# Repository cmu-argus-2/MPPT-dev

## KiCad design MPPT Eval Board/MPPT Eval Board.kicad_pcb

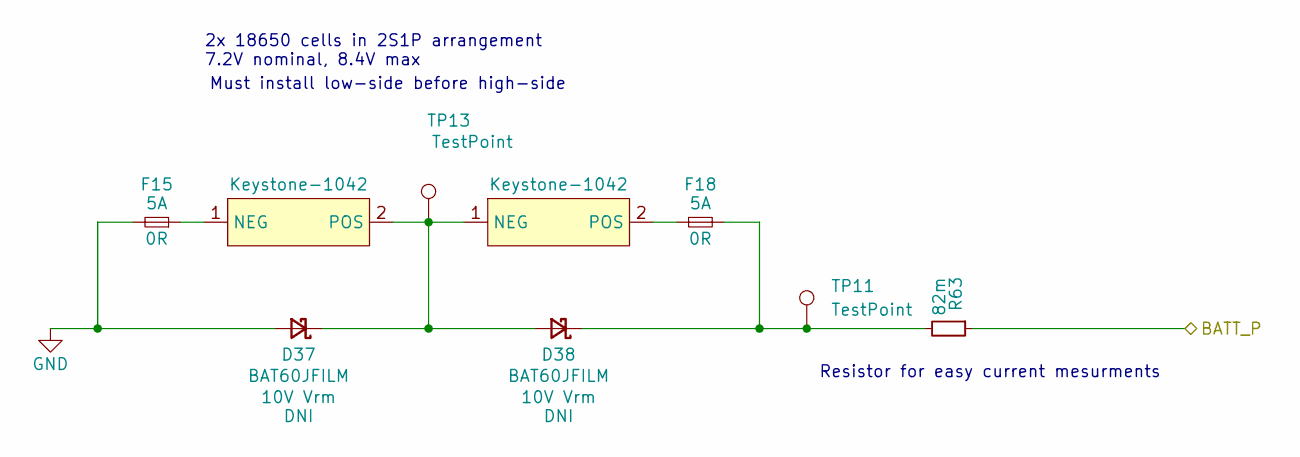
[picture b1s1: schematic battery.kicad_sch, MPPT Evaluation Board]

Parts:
D37, D38: BAT60JFILM; D_SOD-323_HandSoldering
F15, F18: 5A; Fuse_1206_3216Metric; MPN C844862
J3, J4: Keystone-1042; Keystone_1042
R63: 82m; R_0603_1608Metric
TP11, TP13: TestPoint; Pin_D1.0mm_L10.0mm

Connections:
/MPPC Implementation/VCHRG: R63.1; also elsewhere on the board
GND: D37.2 (A), F15.2; also elsewhere on the board
unnamed: D37.1 (K), D38.2 (A), J3.2 (POS), J4.1 (NEG), TP13.1 (1_1)
unnamed: D38.1 (K), F18.2, R63.2, TP11.1 (1_1)
unnamed: F15.1, J3.1 (NEG)
unnamed: F18.1, J4.2 (POS)

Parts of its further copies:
D39, D40: BAT60JFILM; D_SOD-323_HandSoldering
F16, F19: 5A; Fuse_1206_3216Metric; MPN C844862
J5, J6: Keystone-1042; Keystone_1042
R64: 82m; R_0603_1608Metric
TP12, TP14: TestPoint; Pin_D1.0mm_L10.0mm

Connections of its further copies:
/MPPT Implementation/VCHRG: R64.1; also elsewhere on the board
GND: D39.2 (A), F16.2; also elsewhere on the board
unnamed: D39.1 (K), D40.2 (A), J5.2 (POS), J6.1 (NEG), TP14.1 (1_1)
unnamed: D40.1 (K), F19.2, R64.2, TP12.1 (1_1)
unnamed: F16.1, J5.1 (NEG)
unnamed: F19.1, J6.2 (POS)

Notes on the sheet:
Must install low-side before high-side
Resistor for easy current mesurments
2x 18650 cells in 2S1P arrangement 7.2V nominal, 8.4V max

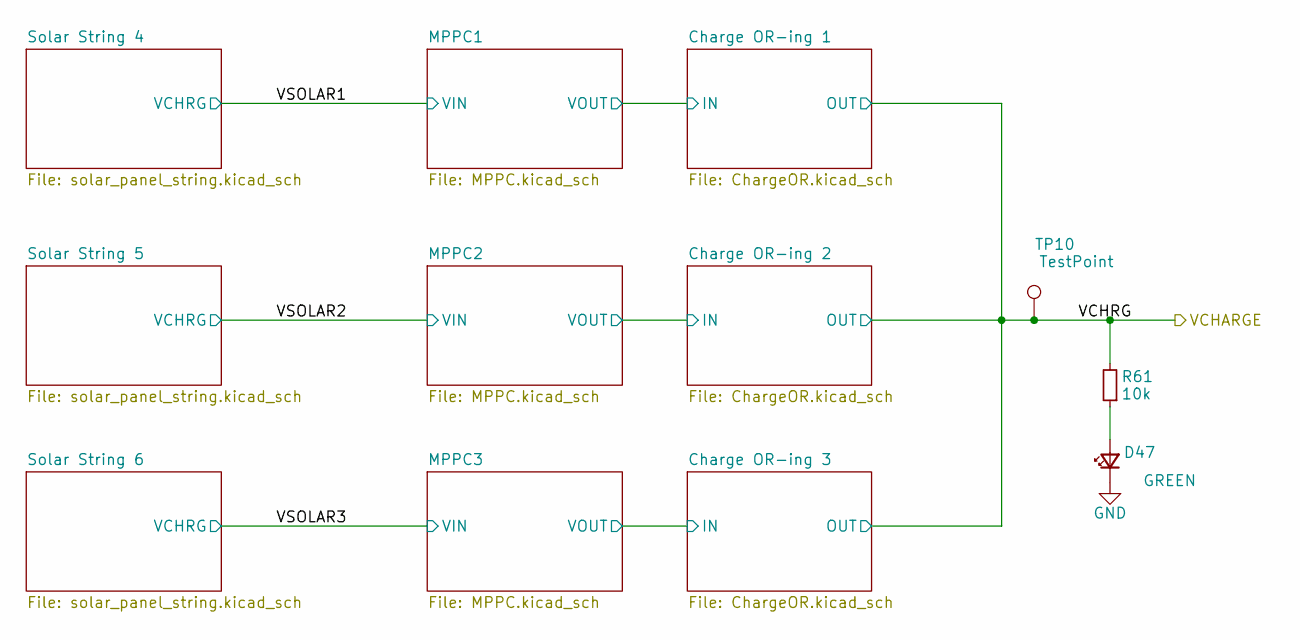
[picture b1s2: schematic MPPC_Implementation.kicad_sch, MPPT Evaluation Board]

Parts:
D47: GREEN; LED_0603_1608Metric; MPN C2909774
R61: 10k; R_0603_1608Metric; MPN C2479067
TP10: TestPoint; Pin_D1.0mm_L10.0mm

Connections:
/MPPC Implementation/VCHRG: R61.2, TP10.1 (1_1); also elsewhere on the board
GND: D47.1 (K); also elsewhere on the board
unnamed: D47.2 (A), R61.1

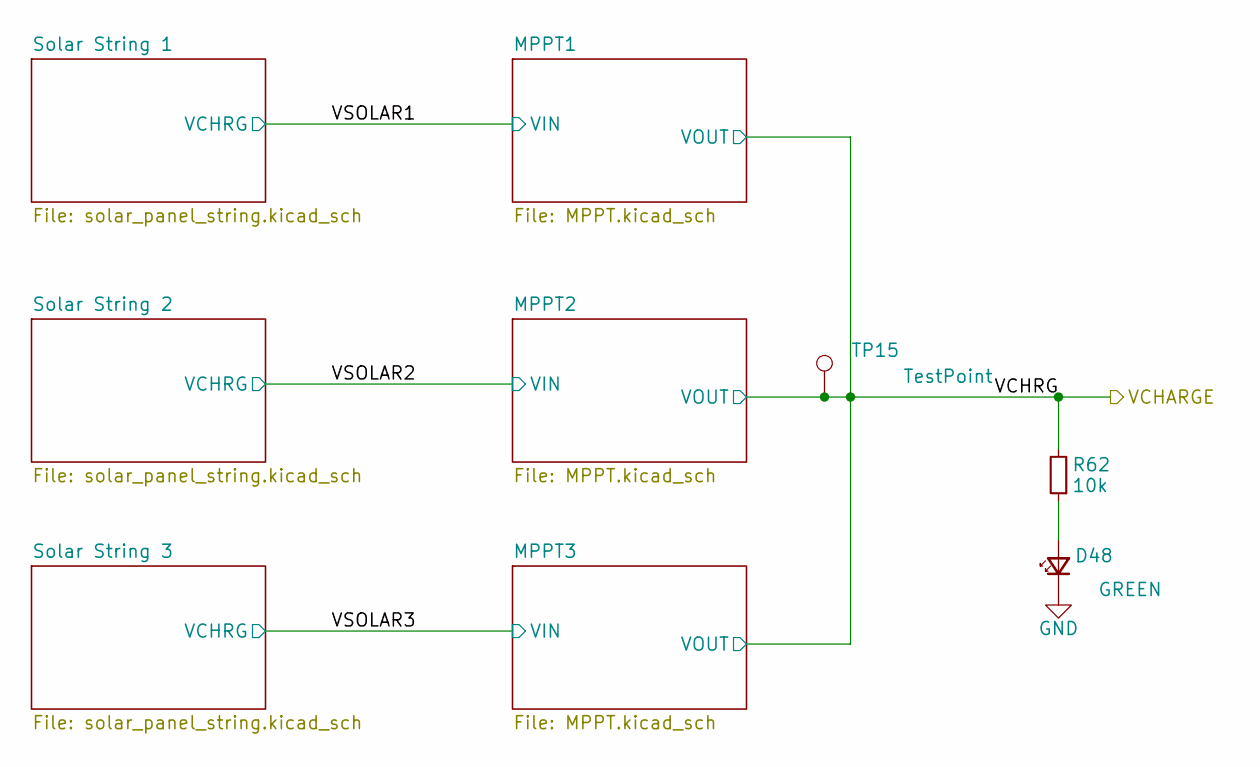
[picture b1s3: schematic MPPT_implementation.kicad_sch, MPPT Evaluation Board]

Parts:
D48: GREEN; LED_0603_1608Metric; MPN C2909774
R62: 10k; R_0603_1608Metric; MPN C2479067
TP15: TestPoint; Pin_D1.0mm_L10.0mm

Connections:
/MPPT Implementation/VCHRG: R62.2, TP15.1 (1_1); also elsewhere on the board
GND: D48.1 (K); also elsewhere on the board
unnamed: D48.2 (A), R62.1

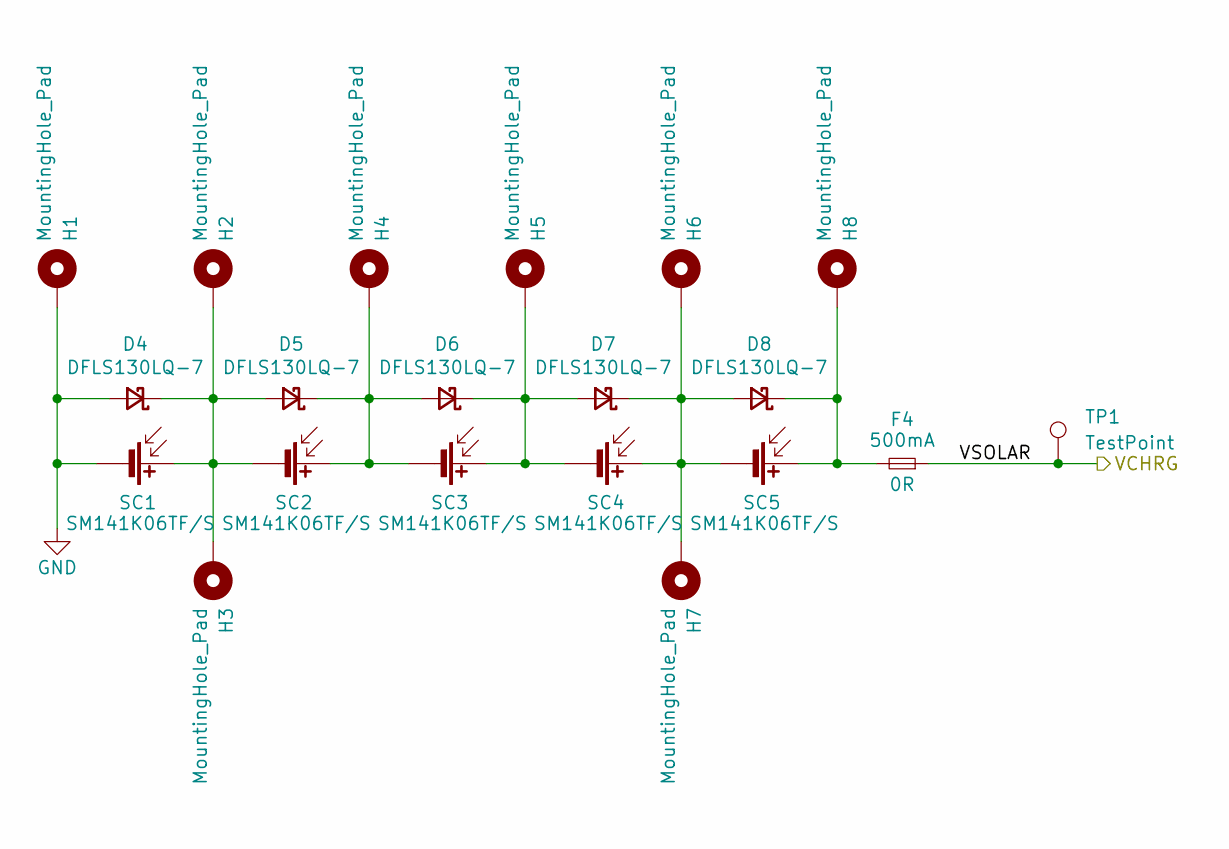
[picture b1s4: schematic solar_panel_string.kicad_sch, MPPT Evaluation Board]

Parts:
D4, D5, D6, D7, D8: DFLS130LQ-7; D_PowerDI-123
F4: 500mA; Fuse_0603_1608Metric
H1, H2, H3, H4, H5, H6, H7, H8: MountingHole_Pad; TestPoint_Pad_D1.0mm
SC1, SC2, SC3, SC4, SC5: SM141K06TF/S; SM141K06TF_S
TP1: TestPoint; Pin_D1.0mm_L10.0mm

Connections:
/MPPT Implementation/VSOLAR2: F4.1, TP1.1 (1_1); also elsewhere on the board
GND: D4.2 (A), H1.1 (1_1), SC1.2 (-); also elsewhere on the board
unnamed: D4.1 (K), D5.2 (A), H2.1 (1_1), H3.1 (1_1), SC1.1 (+), SC2.2 (-)
unnamed: D5.1 (K), D6.2 (A), H4.1 (1_1), SC2.1 (+), SC3.2 (-)
unnamed: D6.1 (K), D7.2 (A), H5.1 (1_1), SC3.1 (+), SC4.2 (-)
unnamed: D7.1 (K), D8.2 (A), H6.1 (1_1), H7.1 (1_1), SC4.1 (+), SC5.2 (-)
unnamed: D8.1 (K), F4.2, H8.1 (1_1), SC5.1 (+)

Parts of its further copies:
D10, D11, D12, D13, D14, D15, D16, D17, D18, D19, D22, D23, D24, D25, D26, D27, D28, D29, D30, D31, D32, D33, D34, D35, D36: DFLS130LQ-7; D_PowerDI-123
F6, F7, F10, F11, F12: 500mA; Fuse_0603_1608Metric
H9, H10, H11, H12, H13, H14, H15, H16, H17, H18, H19, H20, H21, H22, H23, H24, H25, H26, H27, H28, H29, H30, H31, H32, H33, H34, H35, H36, H37, H38, H39, H40, H41, H42, H43, H44, H45, H46, H47, H48: MountingHole_Pad; TestPoint_Pad_D1.0mm
SC6, SC7, SC8, SC9, SC10, SC11, SC12, SC13, SC14, SC15, SC16, SC17, SC18, SC19, SC20, SC21, SC22, SC23, SC24, SC25, SC26, SC27, SC28, SC29, SC30: SM141K06TF/S; SM141K06TF_S
TP2, TP3, TP4, TP5, TP6: TestPoint; Pin_D1.0mm_L10.0mm

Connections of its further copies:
/MPPC Implementation/VSOLAR1: F10.1, TP4.1 (1_1); also elsewhere on the board
/MPPC Implementation/VSOLAR2: F11.1, TP5.1 (1_1); also elsewhere on the board
/MPPC Implementation/VSOLAR3: F12.1, TP6.1 (1_1); also elsewhere on the board
/MPPT Implementation/VSOLAR1: F6.1, TP2.1 (1_1); also elsewhere on the board
/MPPT Implementation/VSOLAR3: F7.1, TP3.1 (1_1); also elsewhere on the board
GND: D10.2 (A), D15.2 (A), D22.2 (A), D27.2 (A), D32.2 (A), H9.1 (1_1), H17.1 (1_1), H25.1 (1_1), H33.1 (1_1), H41.1 (1_1), SC6.2 (-), SC11.2 (-), SC16.2 (-), SC21.2 (-), SC26.2 (-); also elsewhere on the board
unnamed: D10.1 (K), D11.2 (A), H10.1 (1_1), H11.1 (1_1), SC6.1 (+), SC7.2 (-)
unnamed: D11.1 (K), D12.2 (A), H12.1 (1_1), SC7.1 (+), SC8.2 (-)
unnamed: D12.1 (K), D13.2 (A), H13.1 (1_1), SC8.1 (+), SC9.2 (-)
unnamed: D13.1 (K), D14.2 (A), H14.1 (1_1), H15.1 (1_1), SC9.1 (+), SC10.2 (-)
unnamed: D14.1 (K), F6.2, H16.1 (1_1), SC10.1 (+)
unnamed: D15.1 (K), D16.2 (A), H18.1 (1_1), H19.1 (1_1), SC11.1 (+), SC12.2 (-)
unnamed: D16.1 (K), D17.2 (A), H20.1 (1_1), SC12.1 (+), SC13.2 (-)
unnamed: D17.1 (K), D18.2 (A), H21.1 (1_1), SC13.1 (+), SC14.2 (-)
unnamed: D18.1 (K), D19.2 (A), H22.1 (1_1), H23.1 (1_1), SC14.1 (+), SC15.2 (-)
unnamed: D19.1 (K), F7.2, H24.1 (1_1), SC15.1 (+)
unnamed: D22.1 (K), D23.2 (A), H26.1 (1_1), H27.1 (1_1), SC16.1 (+), SC17.2 (-)
unnamed: D23.1 (K), D24.2 (A), H28.1 (1_1), SC17.1 (+), SC18.2 (-)
unnamed: D24.1 (K), D25.2 (A), H29.1 (1_1), SC18.1 (+), SC19.2 (-)
unnamed: D25.1 (K), D26.2 (A), H30.1 (1_1), H31.1 (1_1), SC19.1 (+), SC20.2 (-)
unnamed: D26.1 (K), F10.2, H32.1 (1_1), SC20.1 (+)
unnamed: D27.1 (K), D28.2 (A), H34.1 (1_1), H35.1 (1_1), SC21.1 (+), SC22.2 (-)
unnamed: D28.1 (K), D29.2 (A), H36.1 (1_1), SC22.1 (+), SC23.2 (-)
unnamed: D29.1 (K), D30.2 (A), H37.1 (1_1), SC23.1 (+), SC24.2 (-)
unnamed: D30.1 (K), D31.2 (A), H38.1 (1_1), H39.1 (1_1), SC24.1 (+), SC25.2 (-)
unnamed: D31.1 (K), F11.2, H40.1 (1_1), SC25.1 (+)
unnamed: D32.1 (K), D33.2 (A), H42.1 (1_1), H43.1 (1_1), SC26.1 (+), SC27.2 (-)
unnamed: D33.1 (K), D34.2 (A), H44.1 (1_1), SC27.1 (+), SC28.2 (-)
unnamed: D34.1 (K), D35.2 (A), H45.1 (1_1), SC28.1 (+), SC29.2 (-)
unnamed: D35.1 (K), D36.2 (A), H46.1 (1_1), H47.1 (1_1), SC29.1 (+), SC30.2 (-)
unnamed: D36.1 (K), F12.2, H48.1 (1_1), SC30.1 (+)

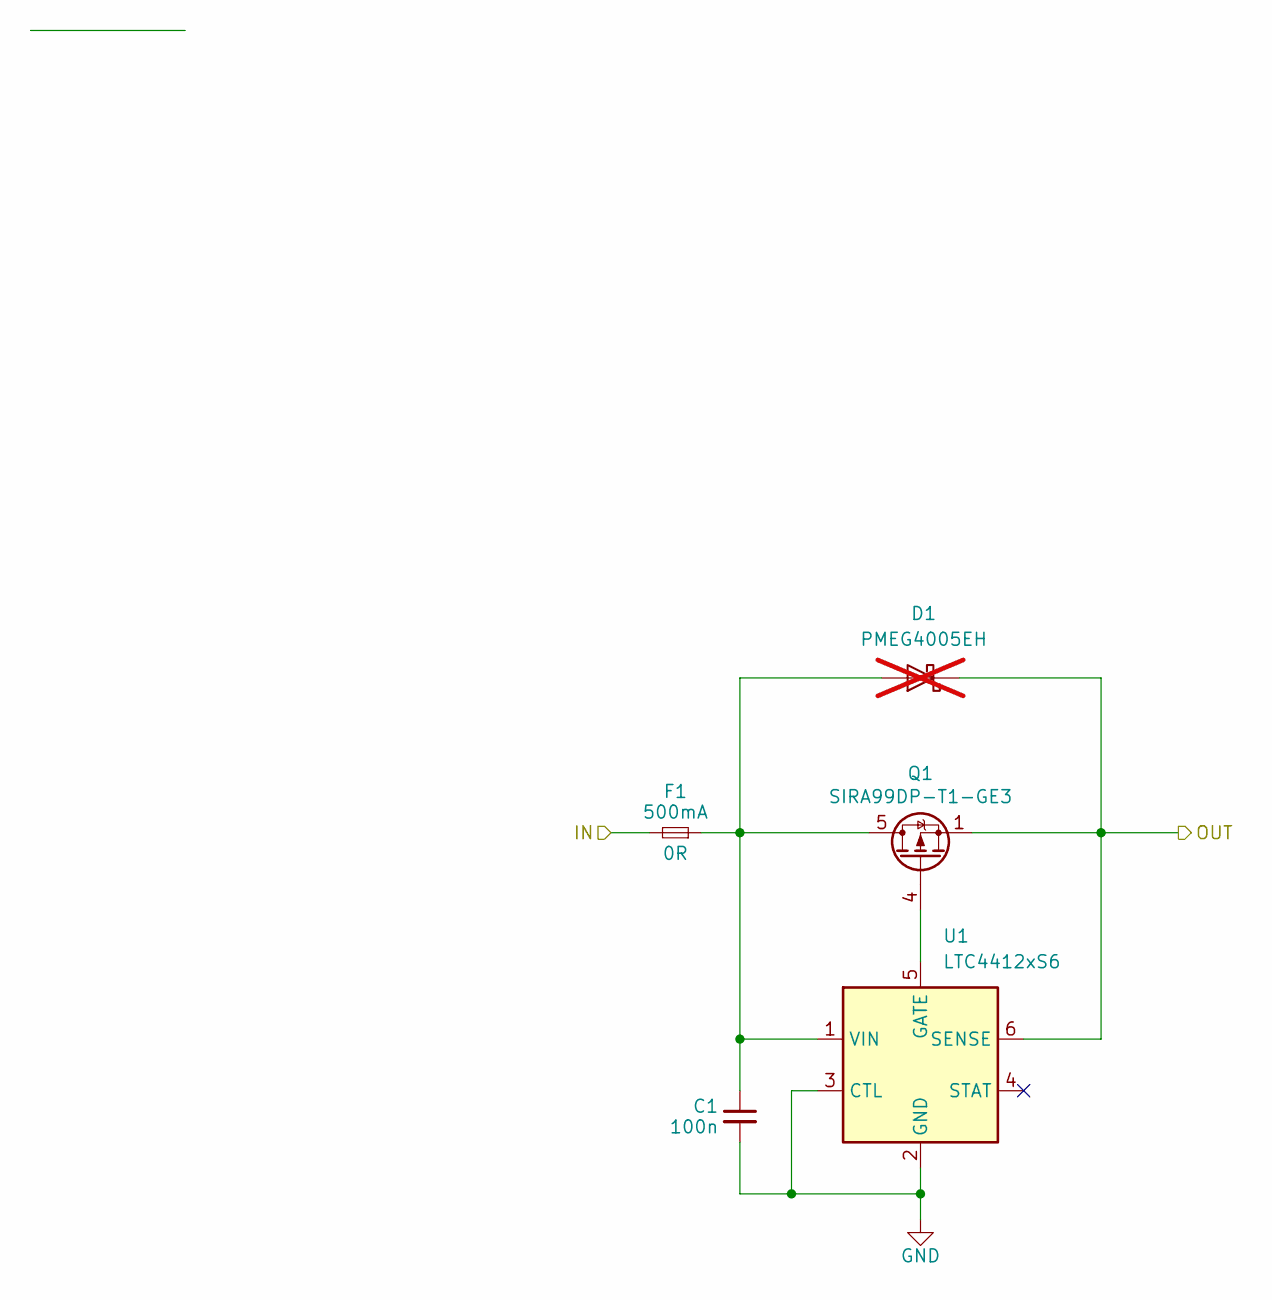
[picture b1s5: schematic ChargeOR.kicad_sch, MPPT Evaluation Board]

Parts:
C1: 100n; C_0603_1608Metric; MPN C307348
D1: PMEG4005EH; D_SOD-123F; not fitted
F1: 500mA; Fuse_0603_1608Metric
Q1: SIRA99DP-T1-GE3; PowerPAK_SO-8_Single; MPN C3289459
U1: LTC4412xS6; TSOT-23-6

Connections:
/MPPC Implementation/Charge OR-ing 1/IN: F1.2; also elsewhere on the board
/MPPC Implementation/VCHRG: D1.1 (K), Q1.1 (S), Q1.2 (S), Q1.3 (S), U1.6 (SENSE); also elsewhere on the board
GND: C1.2, U1.2 (GND), U1.3 (CTL); also elsewhere on the board
unnamed: C1.1, D1.2 (A), F1.1, Q1.5 (D), U1.1 (VIN)
unnamed: Q1.4 (G), U1.5 (GATE)

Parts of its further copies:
C17, C18: 100n; C_0603_1608Metric; MPN C307348
D20, D21: PMEG4005EH; D_SOD-123F; not fitted
F8, F9: 500mA; Fuse_0603_1608Metric
Q11, Q12: SIRA99DP-T1-GE3; PowerPAK_SO-8_Single; MPN C3289459
U8, U9: LTC4412xS6; TSOT-23-6

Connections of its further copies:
/MPPC Implementation/Charge OR-ing 2/IN: F8.2; also elsewhere on the board
/MPPC Implementation/Charge OR-ing 3/IN: F9.2; also elsewhere on the board
/MPPC Implementation/VCHRG: D20.1 (K), D21.1 (K), Q11.1 (S), Q11.2 (S), Q11.3 (S), Q12.1 (S), Q12.2 (S), Q12.3 (S), U8.6 (SENSE), U9.6 (SENSE); also elsewhere on the board
GND: C17.2, C18.2, U8.2 (GND), U8.3 (CTL), U9.2 (GND), U9.3 (CTL); also elsewhere on the board
unnamed: C17.1, D20.2 (A), F8.1, Q11.5 (D), U8.1 (VIN)
unnamed: C18.1, D21.2 (A), F9.1, Q12.5 (D), U9.1 (VIN)
unnamed: Q11.4 (G), U8.5 (GATE)
unnamed: Q12.4 (G), U9.5 (GATE)

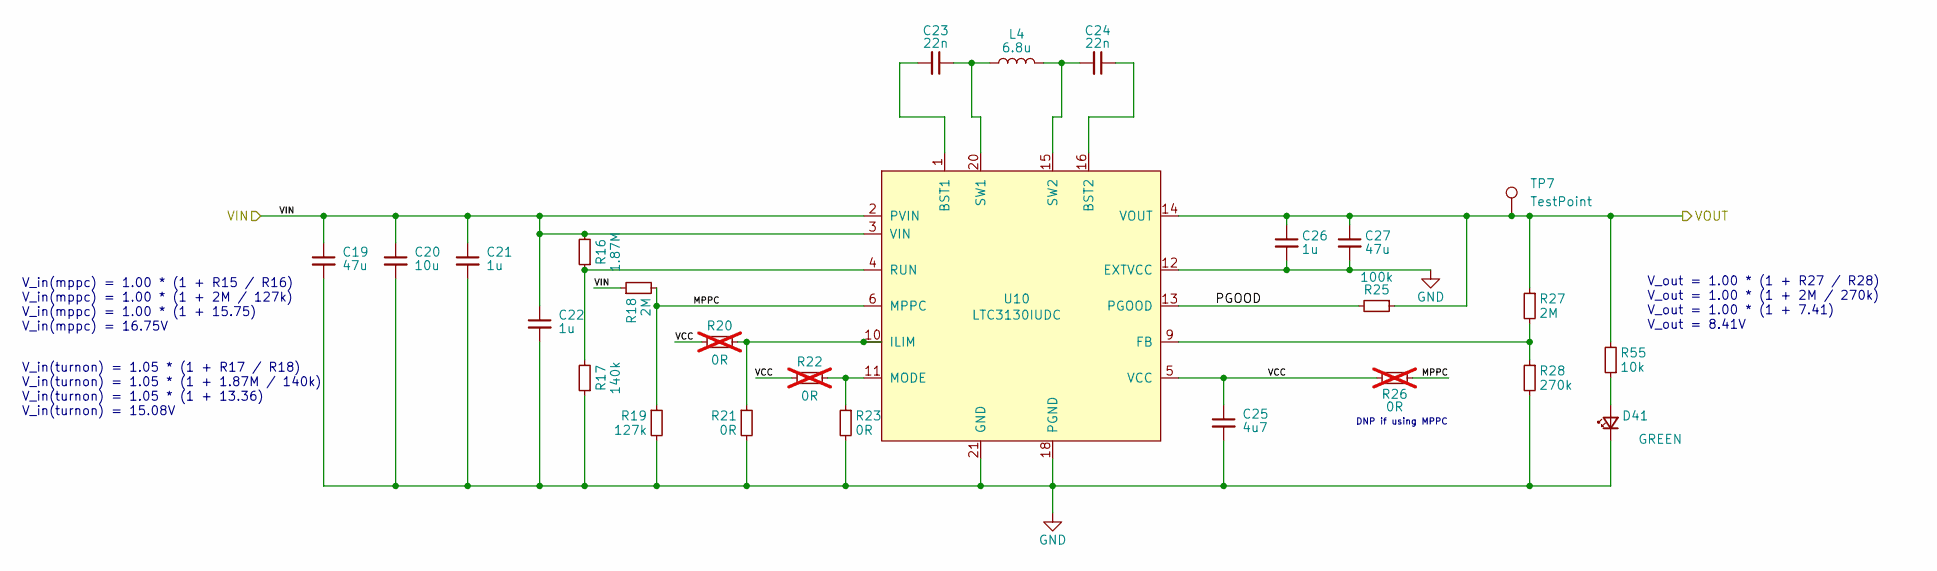
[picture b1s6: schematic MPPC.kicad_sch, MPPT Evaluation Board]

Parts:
C19, C27: 47u; C_1210_3225Metric; Voltage 16V; Mfr. # GRM32EC81C476KE15L
C20: 10u; C_1210_3225Metric; MPN C126617
C21, C22, C26: 1u; C_0805_2012Metric; MPN C126592
C23, C24: 22n; C_0603_1608Metric; MPN C161234
C25: 4u7; C_0603_1608Metric; MPN C437575
D41: GREEN; LED_0603_1608Metric; MPN C2909774
L4: 6.8u; L_Coilcraft_LPS4018; Mfr. # LPS4018-472
R16: 1.87M; R_0603_1608Metric
R17: 140k; R_0603_1608Metric
R18, R27: 2M; R_0603_1608Metric
R19: 127k; R_0603_1608Metric
R20, R22: 0R; R_0603_1608Metric; Mfr. # RK73Z1JTTD; not fitted
R21, R23: 0R; R_0603_1608Metric; MPN C844915
R25: 100k; R_0603_1608Metric; MPN C237792
R26: 0R; R_0603_1608Metric; MPN C237792; not fitted
R28: 270k; R_0603_1608Metric; MPN C118142
R55: 10k; R_0603_1608Metric; MPN C2479067
TP7: TestPoint; Pin_D1.0mm_L10.0mm
U10: LTC3130IUDC; QFN-20-1EP_3x4mm_P0.5mm_EP1.65x2.65mm; MPN C684244

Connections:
/MPPC Implementation/Charge OR-ing 1/IN: C26.1, C27.1, R25.1, R27.1, R55.2, TP7.1 (1_1), U10.14 (VOUT); also elsewhere on the board
/MPPC Implementation/MPPC1/MPPC: R18.2, R19.1, R26.2, U10.6 (MPPC)
/MPPC Implementation/MPPC1/PGOOD: R25.2, U10.13 (PGOOD)
/MPPC Implementation/MPPC1/VCC: C25.1, R20.2, R22.2, R26.1, U10.5 (VCC)
/MPPC Implementation/VSOLAR1: C19.1, C20.1, C21.1, C22.1, R16.2, R18.1, U10.2 (PVIN), U10.3 (VIN); also elsewhere on the board
GND: C19.2, C20.2, C21.2, C22.2, C25.2, C26.2, C27.2, D41.1 (K), R17.1, R19.2, R21.2, R23.2, R28.2, U10.7 (GND), U10.8 (GND), U10.12 (EXTVCC), U10.17 (GND), U10.18 (PGND), U10.19 (PGND), U10.21 (GND); also elsewhere on the board
unnamed: D41.2 (A), R55.1
unnamed: C23.2, U10.1 (BST1)
unnamed: C24.1, U10.16 (BST2)
unnamed: R27.2, R28.1, U10.9 (FB)
unnamed: R20.1, R21.1, U10.10 (ILIM)
unnamed: R22.1, R23.1, U10.11 (MODE)
unnamed: R16.1, R17.2, U10.4 (RUN)
unnamed: C23.1, L4.1, U10.20 (SW1)
unnamed: C24.2, L4.2, U10.15 (SW2)

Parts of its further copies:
C28, C36, C37, C45: 47u; C_1210_3225Metric; Voltage 16V; Mfr. # GRM32EC81C476KE15L
C29, C38: 10u; C_1210_3225Metric; MPN C126617
C30, C31, C35, C39, C40, C44: 1u; C_0805_2012Metric; MPN C126592
C32, C33, C41, C42: 22n; C_0603_1608Metric; MPN C161234
C34, C43: 4u7; C_0603_1608Metric; MPN C437575
D42, D43: GREEN; LED_0603_1608Metric; MPN C2909774
L5, L6: 6.8u; L_Coilcraft_LPS4018; Mfr. # LPS4018-472
R29, R42: 1.87M; R_0603_1608Metric
R30, R43: 140k; R_0603_1608Metric
R31, R40, R44, R53: 2M; R_0603_1608Metric
R32, R45: 127k; R_0603_1608Metric
R33, R35, R46, R48: 0R; R_0603_1608Metric; Mfr. # RK73Z1JTTD; not fitted
R34, R36, R47, R49: 0R; R_0603_1608Metric; MPN C844915
R38, R51: 100k; R_0603_1608Metric; MPN C237792
R39, R52: 0R; R_0603_1608Metric; MPN C237792; not fitted
R41, R54: 270k; R_0603_1608Metric; MPN C118142
R56, R57: 10k; R_0603_1608Metric; MPN C2479067
TP8, TP9: TestPoint; Pin_D1.0mm_L10.0mm
U11, U12: LTC3130IUDC; QFN-20-1EP_3x4mm_P0.5mm_EP1.65x2.65mm; MPN C684244

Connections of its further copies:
/MPPC Implementation/Charge OR-ing 2/IN: C35.1, C36.1, R38.1, R40.1, R56.2, TP8.1 (1_1), U11.14 (VOUT); also elsewhere on the board
/MPPC Implementation/Charge OR-ing 3/IN: C44.1, C45.1, R51.1, R53.1, R57.2, TP9.1 (1_1), U12.14 (VOUT); also elsewhere on the board
/MPPC Implementation/MPPC2/MPPC: R31.2, R32.1, R39.2, U11.6 (MPPC)
/MPPC Implementation/MPPC2/PGOOD: R38.2, U11.13 (PGOOD)
/MPPC Implementation/MPPC2/VCC: C34.1, R33.2, R35.2, R39.1, U11.5 (VCC)
/MPPC Implementation/MPPC3/MPPC: R44.2, R45.1, R52.2, U12.6 (MPPC)
/MPPC Implementation/MPPC3/PGOOD: R51.2, U12.13 (PGOOD)
/MPPC Implementation/MPPC3/VCC: C43.1, R46.2, R48.2, R52.1, U12.5 (VCC)
/MPPC Implementation/VSOLAR2: C28.1, C29.1, C30.1, C31.1, R29.2, R31.1, U11.2 (PVIN), U11.3 (VIN); also elsewhere on the board
/MPPC Implementation/VSOLAR3: C37.1, C38.1, C39.1, C40.1, R42.2, R44.1, U12.2 (PVIN), U12.3 (VIN); also elsewhere on the board
GND: C28.2, C29.2, C30.2, C31.2, C34.2, C35.2, C36.2, C37.2, C38.2, C39.2, C40.2, C43.2, C44.2, C45.2, D42.1 (K), D43.1 (K), R30.1, R32.2, R34.2, R36.2, R41.2, R43.1, R45.2, R47.2, R49.2, R54.2, U11.7 (GND), U11.8 (GND), U11.12 (EXTVCC), U11.17 (GND), U11.18 (PGND), U11.19 (PGND), U11.21 (GND), U12.7 (GND), U12.8 (GND), U12.12 (EXTVCC), U12.17 (GND), U12.18 (PGND), U12.19 (PGND), U12.21 (GND); also elsewhere on the board
unnamed: D42.2 (A), R56.1
unnamed: D43.2 (A), R57.1
unnamed: C32.2, U11.1 (BST1)
unnamed: C33.1, U11.16 (BST2)
unnamed: R40.2, R41.1, U11.9 (FB)
unnamed: R33.1, R34.1, U11.10 (ILIM)
unnamed: R35.1, R36.1, U11.11 (MODE)
unnamed: R29.1, R30.2, U11.4 (RUN)
unnamed: C32.1, L5.1, U11.20 (SW1)
unnamed: C33.2, L5.2, U11.15 (SW2)
unnamed: C41.2, U12.1 (BST1)
unnamed: C42.1, U12.16 (BST2)
unnamed: R53.2, R54.1, U12.9 (FB)
unnamed: R46.1, R47.1, U12.10 (ILIM)
unnamed: R48.1, R49.1, U12.11 (MODE)
unnamed: R42.1, R43.2, U12.4 (RUN)
unnamed: C41.1, L6.1, U12.20 (SW1)
unnamed: C42.2, L6.2, U12.15 (SW2)

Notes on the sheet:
DNP if using MPPC
V_out = 1.00 * (1 + R27 / R28) V_out = 1.00 * (1 + 2M / 270k) V_out = 1.00 * (1 + 7.41) V_out = 8.41V
V_in(turnon) = 1.05 * (1 + R17 / R18) V_in(turnon) = 1.05 * (1 + 1.87M / 140k) V_in(turnon) = 1.05 * (1 + 13.36) V_in(turnon) = 15.08V
V_in(mppc) = 1.00 * (1 + R15 / R16) V_in(mppc) = 1.00 * (1 + 2M / 127k) V_in(mppc) = 1.00 * (1 + 15.75) V_in(mppc) = 16.75V

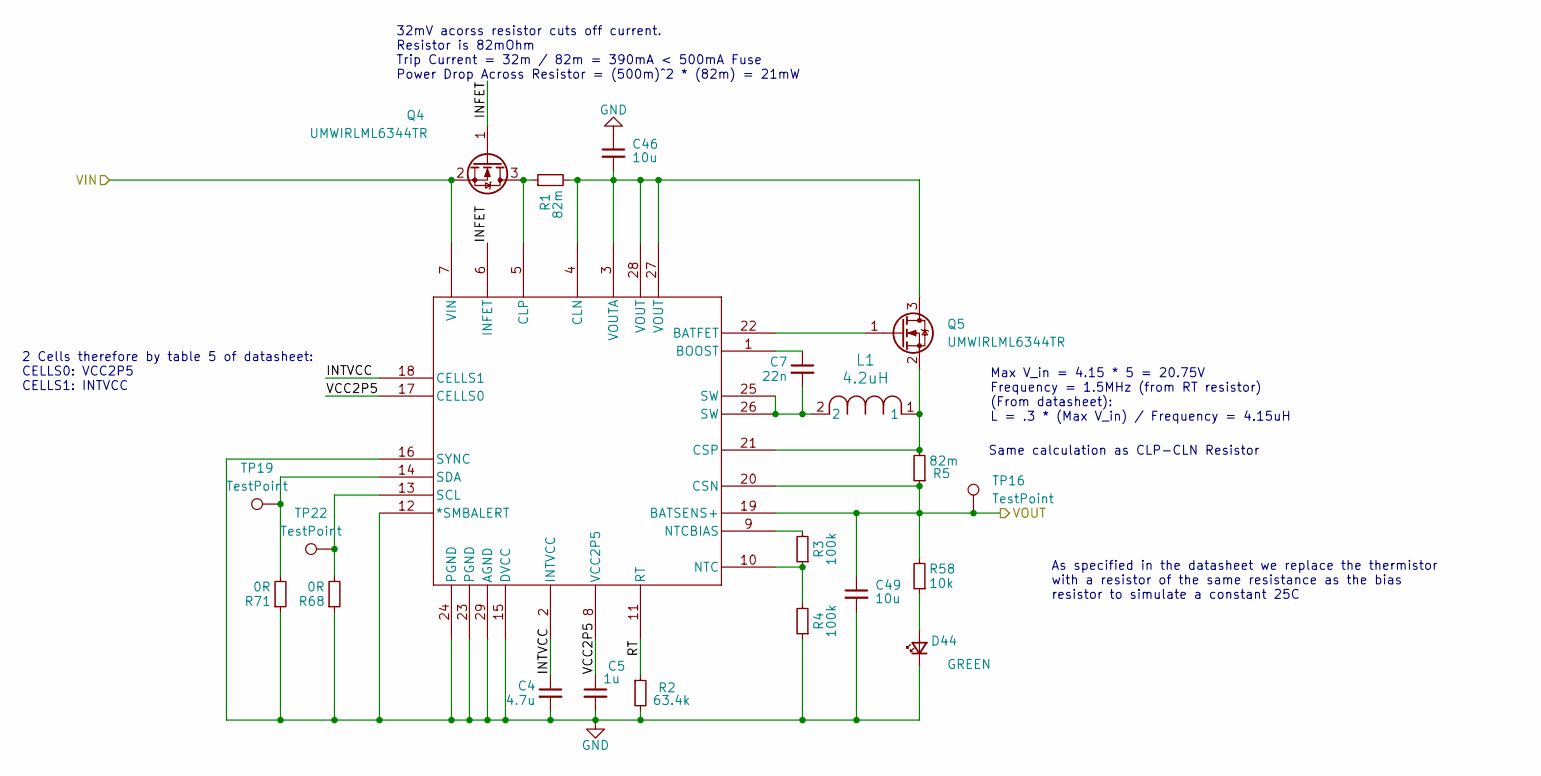
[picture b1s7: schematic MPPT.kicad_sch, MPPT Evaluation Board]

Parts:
C4: 4.7u; C_0603_1608Metric; MPN CL10A475KO8NNNC
C5: 1u; C_0603_1608Metric; MPN CL10A105KB8NNNC
C7: 22n; C_0603_1608Metric; MPN CL10B223KB8NNNC
C46, C49: 10u; C_1210_3225Metric; MPN C126617
D44: GREEN; LED_0603_1608Metric; MPN C2909774
L1: 4.2uH; IND_R2NC_SUM
Q4, Q5: UMWIRLML6344TR; SOT-23
R1, R5: 82m; R_0603_1608Metric
R2: 63.4k; R_0603_1608Metric
R3, R4: 100k; R_0603_1608Metric; MPN C237792
R58: 10k; R_0603_1608Metric; MPN C2479067
R68, R71: 0R; R_0603_1608Metric; MPN C844915
TP16, TP19, TP22: TestPoint; Pin_D1.0mm_L10.0mm
U4: LTC4162EUFD-LAD-TRPBF; 05-08-1712_ADI

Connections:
/MPPT Implementation/MPPT2/INFET: Q4.1 (G), U4.6 (INFET)
/MPPT Implementation/MPPT2/INTVCC: C4.1, U4.2 (INTVCC), U4.18 (CELLS1)
/MPPT Implementation/MPPT2/RT: R2.1, U4.11 (RT)
/MPPT Implementation/MPPT2/VCC2P5: C5.1, U4.8 (VCC2P5), U4.17 (CELLS0)
/MPPT Implementation/VCHRG: C49.1, R5.1, R58.2, TP16.1 (1_1), U4.19 (BATSENS+), U4.20 (CSN); also elsewhere on the board
/MPPT Implementation/VSOLAR2: Q4.2 (S), U4.7 (VIN); also elsewhere on the board
GND: C4.2, C5.2, C46.1, C49.2, D44.1 (K), R2.2, R4.1, R68.1, R71.1, U4.12 (*SMBALERT), U4.15 (DVCC), U4.16 (SYNC), U4.23 (PGND), U4.24 (PGND), U4.29 (AGND); also elsewhere on the board
unnamed: C7.2, L1.2, U4.25 (SW), U4.26 (SW)
unnamed: D44.2 (A), R58.1
unnamed: Q4.3 (D), R1.1, U4.5 (CLP)
unnamed: C46.2, Q5.3 (D), R1.2, U4.3 (VOUTA), U4.4 (CLN), U4.27 (VOUT), U4.28 (VOUT)
unnamed: Q5.1 (G), U4.22 (BATFET)
unnamed: L1.1, Q5.2 (S), R5.2, U4.21 (CSP)
unnamed: C7.1, U4.1 (BOOST)
unnamed: R3.1, R4.2, U4.10 (NTC)
unnamed: R3.2, U4.9 (NTCBIAS)
unnamed: R68.2, TP22.1 (1_1), U4.13 (SCL)
unnamed: R71.2, TP19.1 (1_1), U4.14 (SDA)

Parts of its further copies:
C8, C13: 4.7u; C_0603_1608Metric; MPN CL10A475KO8NNNC
C9, C14: 1u; C_0603_1608Metric; MPN CL10A105KB8NNNC
C11, C16: 22n; C_0603_1608Metric; MPN CL10B223KB8NNNC
C47, C48, C50, C51: 10u; C_1210_3225Metric; MPN C126617
D45, D46: GREEN; LED_0603_1608Metric; MPN C2909774
L2, L3: 4.2uH; IND_R2NC_SUM
Q6, Q7, Q9, Q10: UMWIRLML6344TR; SOT-23
R6, R10, R11, R15: 82m; R_0603_1608Metric
R7, R12: 63.4k; R_0603_1608Metric
R8, R9, R13, R14: 100k; R_0603_1608Metric; MPN C237792
R59, R60: 10k; R_0603_1608Metric; MPN C2479067
R69, R70, R72, R73: 0R; R_0603_1608Metric; MPN C844915
TP17, TP18, TP20, TP21, TP23, TP24: TestPoint; Pin_D1.0mm_L10.0mm
U5, U7: LTC4162EUFD-LAD-TRPBF; 05-08-1712_ADI

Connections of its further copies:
/MPPT Implementation/MPPT1/INFET: Q6.1 (G), U5.6 (INFET)
/MPPT Implementation/MPPT1/INTVCC: C8.1, U5.2 (INTVCC), U5.18 (CELLS1)
/MPPT Implementation/MPPT1/RT: R7.1, U5.11 (RT)
/MPPT Implementation/MPPT1/VCC2P5: C9.1, U5.8 (VCC2P5), U5.17 (CELLS0)
/MPPT Implementation/MPPT3/INFET: Q9.1 (G), U7.6 (INFET)
/MPPT Implementation/MPPT3/INTVCC: C13.1, U7.2 (INTVCC), U7.18 (CELLS1)
/MPPT Implementation/MPPT3/RT: R12.1, U7.11 (RT)
/MPPT Implementation/MPPT3/VCC2P5: C14.1, U7.8 (VCC2P5), U7.17 (CELLS0)
/MPPT Implementation/VCHRG: C50.1, C51.1, R10.1, R15.1, R59.2, R60.2, TP17.1 (1_1), TP18.1 (1_1), U5.19 (BATSENS+), U5.20 (CSN), U7.19 (BATSENS+), U7.20 (CSN); also elsewhere on the board
/MPPT Implementation/VSOLAR1: Q6.2 (S), U5.7 (VIN); also elsewhere on the board
/MPPT Implementation/VSOLAR3: Q9.2 (S), U7.7 (VIN); also elsewhere on the board
GND: C8.2, C9.2, C13.2, C14.2, C47.1, C48.1, C50.2, C51.2, D45.1 (K), D46.1 (K), R7.2, R9.1, R12.2, R14.1, R69.1, R70.1, R72.1, R73.1, U5.12 (*SMBALERT), U5.15 (DVCC), U5.16 (SYNC), U5.23 (PGND), U5.24 (PGND), U5.29 (AGND), U7.12 (*SMBALERT), U7.15 (DVCC), U7.16 (SYNC), U7.23 (PGND), U7.24 (PGND), U7.29 (AGND); also elsewhere on the board
unnamed: C11.2, L2.2, U5.25 (SW), U5.26 (SW)
unnamed: C16.2, L3.2, U7.25 (SW), U7.26 (SW)
unnamed: D45.2 (A), R59.1
unnamed: D46.2 (A), R60.1
unnamed: Q6.3 (D), R6.1, U5.5 (CLP)
unnamed: C47.2, Q7.3 (D), R6.2, U5.3 (VOUTA), U5.4 (CLN), U5.27 (VOUT), U5.28 (VOUT)
unnamed: Q7.1 (G), U5.22 (BATFET)
unnamed: L2.1, Q7.2 (S), R10.2, U5.21 (CSP)
unnamed: Q9.3 (D), R11.1, U7.5 (CLP)
unnamed: C48.2, Q10.3 (D), R11.2, U7.3 (VOUTA), U7.4 (CLN), U7.27 (VOUT), U7.28 (VOUT)
unnamed: Q10.1 (G), U7.22 (BATFET)
unnamed: L3.1, Q10.2 (S), R15.2, U7.21 (CSP)
unnamed: C11.1, U5.1 (BOOST)
unnamed: R8.1, R9.2, U5.10 (NTC)
unnamed: R8.2, U5.9 (NTCBIAS)
unnamed: R69.2, TP23.1 (1_1), U5.13 (SCL)
unnamed: R72.2, TP20.1 (1_1), U5.14 (SDA)
unnamed: C16.1, U7.1 (BOOST)
unnamed: R13.1, R14.2, U7.10 (NTC)
unnamed: R13.2, U7.9 (NTCBIAS)
unnamed: R70.2, TP24.1 (1_1), U7.13 (SCL)
unnamed: R73.2, TP21.1 (1_1), U7.14 (SDA)

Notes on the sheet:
As specified in the datasheet we replace the thermistor with a resistor of the same resistance as the bias resistor to simulate a constant 25C
32mV acorss resistor cuts off current. Resistor is 82mOhm Trip Current = 32m / 82m = 390mA < 500mA Fuse Power Drop Across Resistor = (500m)^2 * (82m) = 21mW
Same calculation as CLP-CLN Resistor
Max V_in = 4.15 * 5 = 20.75V Frequency = 1.5MHz (from RT resistor) (From datasheet): L = .3 * (Max V_in) / Frequency = 4.15uH
2 Cells therefore by table 5 of datasheet: CELLS0: VCC2P5 CELLS1: INTVCC

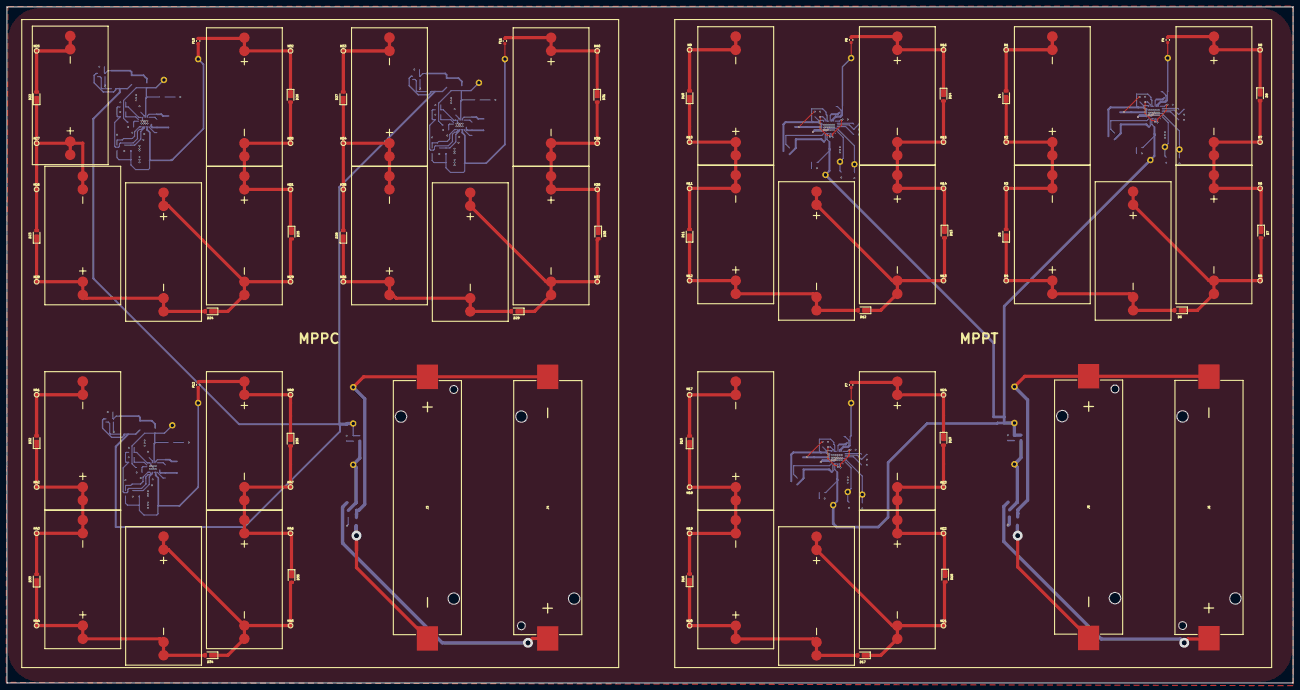
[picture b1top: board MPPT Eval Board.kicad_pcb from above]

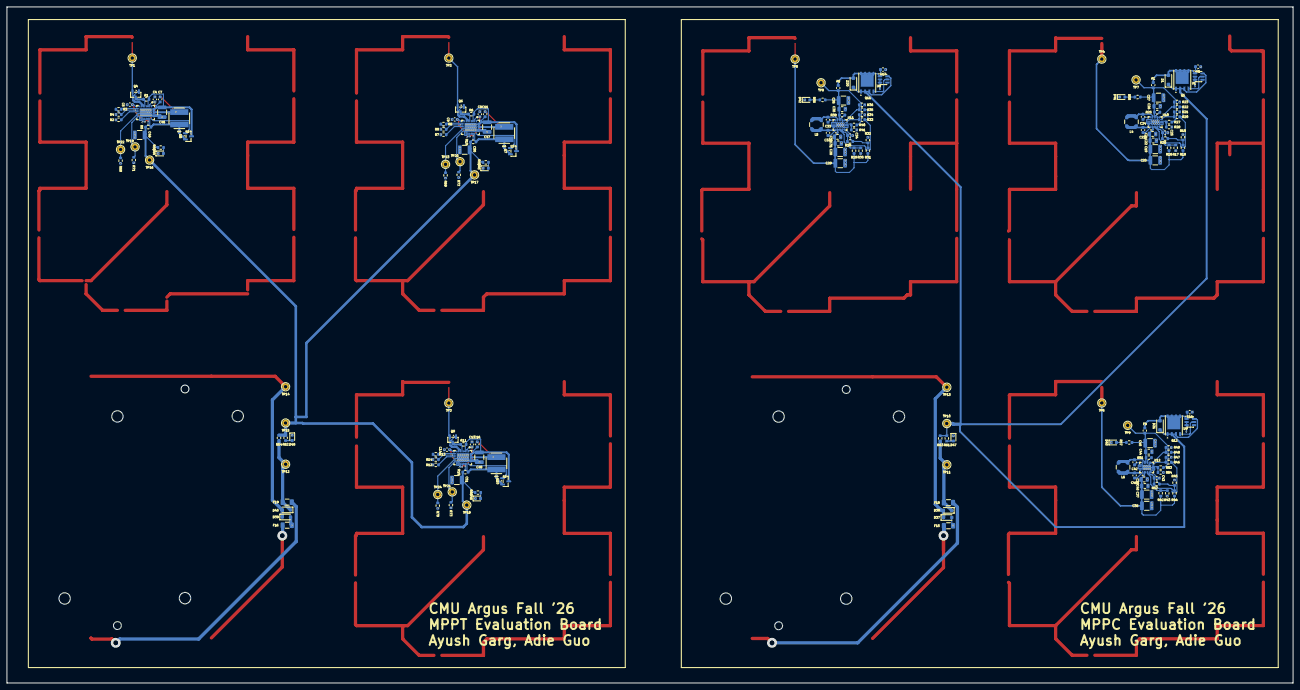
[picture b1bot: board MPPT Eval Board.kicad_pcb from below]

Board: 2 copper layers, 390.0 x 205.0 mm, 300 parts (182 on the bottom side), 139 nets.

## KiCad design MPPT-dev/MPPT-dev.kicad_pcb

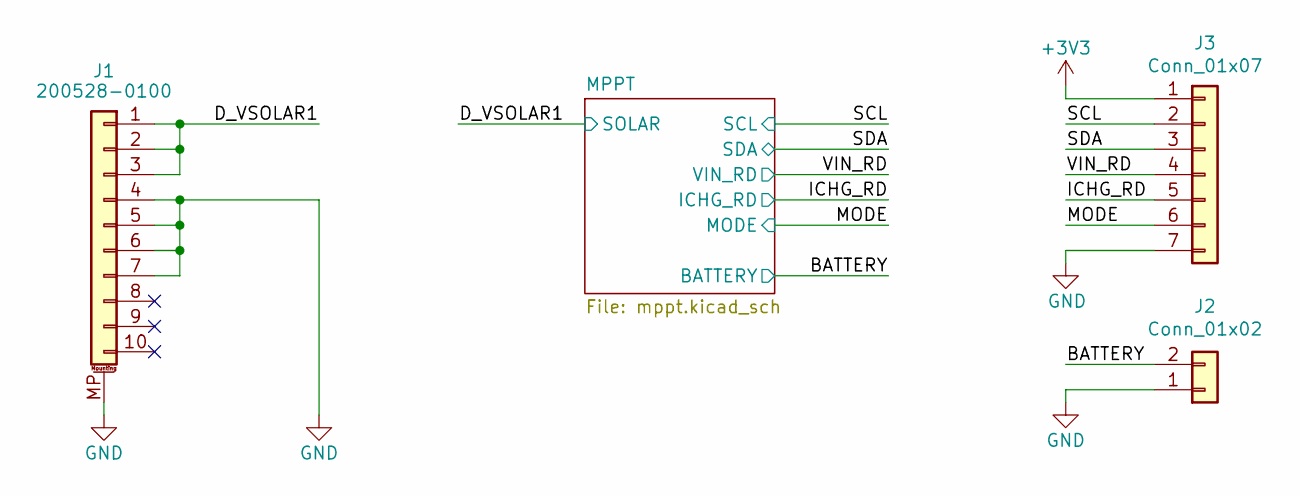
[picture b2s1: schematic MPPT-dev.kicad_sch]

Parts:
J1: 200528-0100; Molex_200528-0100_1x10-1MP_P1.00mm_Horizontal
J2: Conn_01x02; PinHeader_1x02_P2.54mm_Vertical
J3: Conn_01x07; PinHeader_1x07_P2.54mm_Vertical

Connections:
+3V3: J3.1; also elsewhere on the board
/BATTERY: J2.2; also elsewhere on the board
/D_VSOLAR1: J1.1, J1.2, J1.3; also elsewhere on the board
/ICHG_RD: J3.5; also elsewhere on the board
/MODE: J3.6; also elsewhere on the board
/SCL: J3.2; also elsewhere on the board
/SDA: J3.3; also elsewhere on the board
/VIN_RD: J3.4; also elsewhere on the board
GND: J1.4, J1.5, J1.6, J1.7, J1.MP (MountPin), J2.1, J3.7; also elsewhere on the board
